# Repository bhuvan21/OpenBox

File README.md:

# OpenBox  
An open source, arduino based fencing scoring box. Created with a low budget in mind (costs ~£50 to build), but maximal portability and functionality.  

The hardware of this fencing box has been meticulously planned, designed, and put together.  
The software for the box is not yet finished, with only the at-home foil practice, as well as some settings being done.  

## Hardware  
All information on the physical build is contain in BUILD.md, within the build subdirectory.

## Software  
There are quite a few test scripts present in /tests/ which can be used for ensuring that all components connected to the microcontroller are functioning correctly.  
The main box script resides in /main/  

## Roadmap
Though still in the development stage, I think this has the potential to become a viable product. I hope to refine my design further and start deploying them in clubs, schools and tournaments.

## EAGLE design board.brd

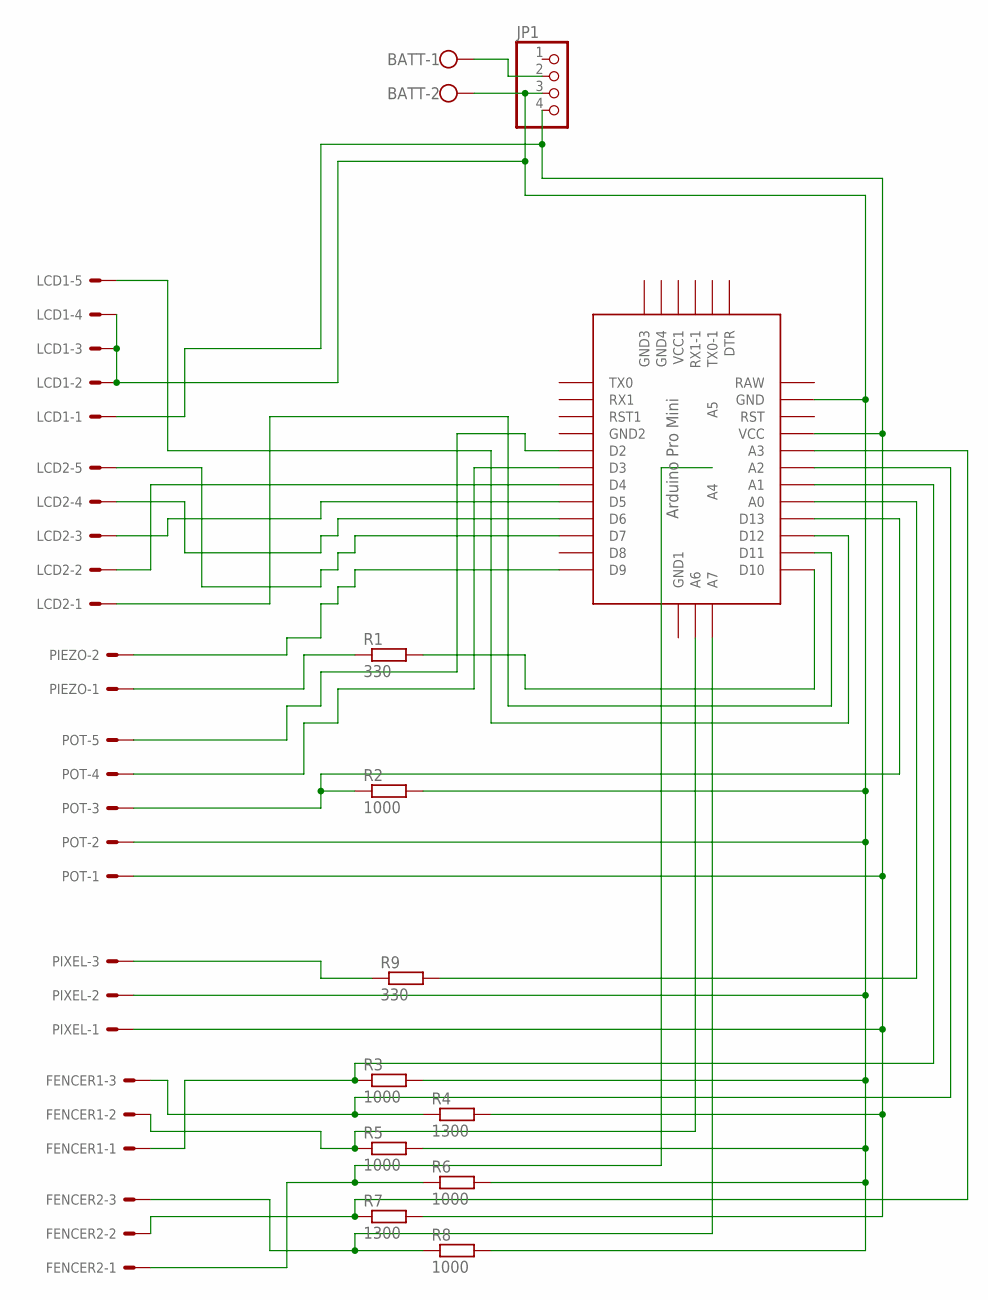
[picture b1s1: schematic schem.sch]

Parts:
BATT: W237-102
FENCER1, FENCER2: 22-27-2031-03; 6410-03
JP1: PINHD-1X4; 1X04
LCD1, LCD2: 22-27-2051-05; 6410-05
PIEZO: 22-27-2021-02; 6410-02
PIXEL: 22-27-2031-03; 6410-03
POT: 22-27-2051-05; 6410-05
R1: 330; 0204/7
R2, R3, R5, R6, R8: 1000; 0204/7
R4, R7: 1300; 0204/7
R9: 330; 0207/10
U$1: ABK-PRO-MINI

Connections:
unnamed: JP1.4, LCD1.1, PIXEL.1, POT.1, R4.2, R7.2, U$1.VCC
unnamed: BATT.2, JP1.3, LCD1.2, LCD1.3, LCD1.4, PIXEL.2, POT.2, R2.2, R3.2, R5.2, R6.2, R8.2, U$1.GND
unnamed: BATT.1, JP1.2
unnamed: LCD2.4, U$1.D6
unnamed: LCD2.1, U$1.D11
unnamed: LCD1.5, U$1.D12
unnamed: LCD2.2, U$1.D4
unnamed: LCD2.3, U$1.D5
unnamed: LCD2.5, U$1.D7
unnamed: PIEZO.2, U$1.D9
unnamed: PIEZO.1, R1.1
unnamed: R1.2, U$1.D10
unnamed: POT.5, U$1.D2
unnamed: POT.4, U$1.D3
unnamed: FENCER1.1, R3.1, U$1.A1
unnamed: POT.3, R2.1, U$1.D13
unnamed: R9.2, U$1.A0
unnamed: FENCER1.3, R4.1, U$1.A2
unnamed: FENCER1.2, R5.1, U$1.A6
unnamed: FENCER2.1, R6.1, U$1.A4
unnamed: FENCER2.3, R8.1, U$1.A7
unnamed: PIXEL.3, R9.1
unnamed: FENCER2.2, R7.1, U$1.A3

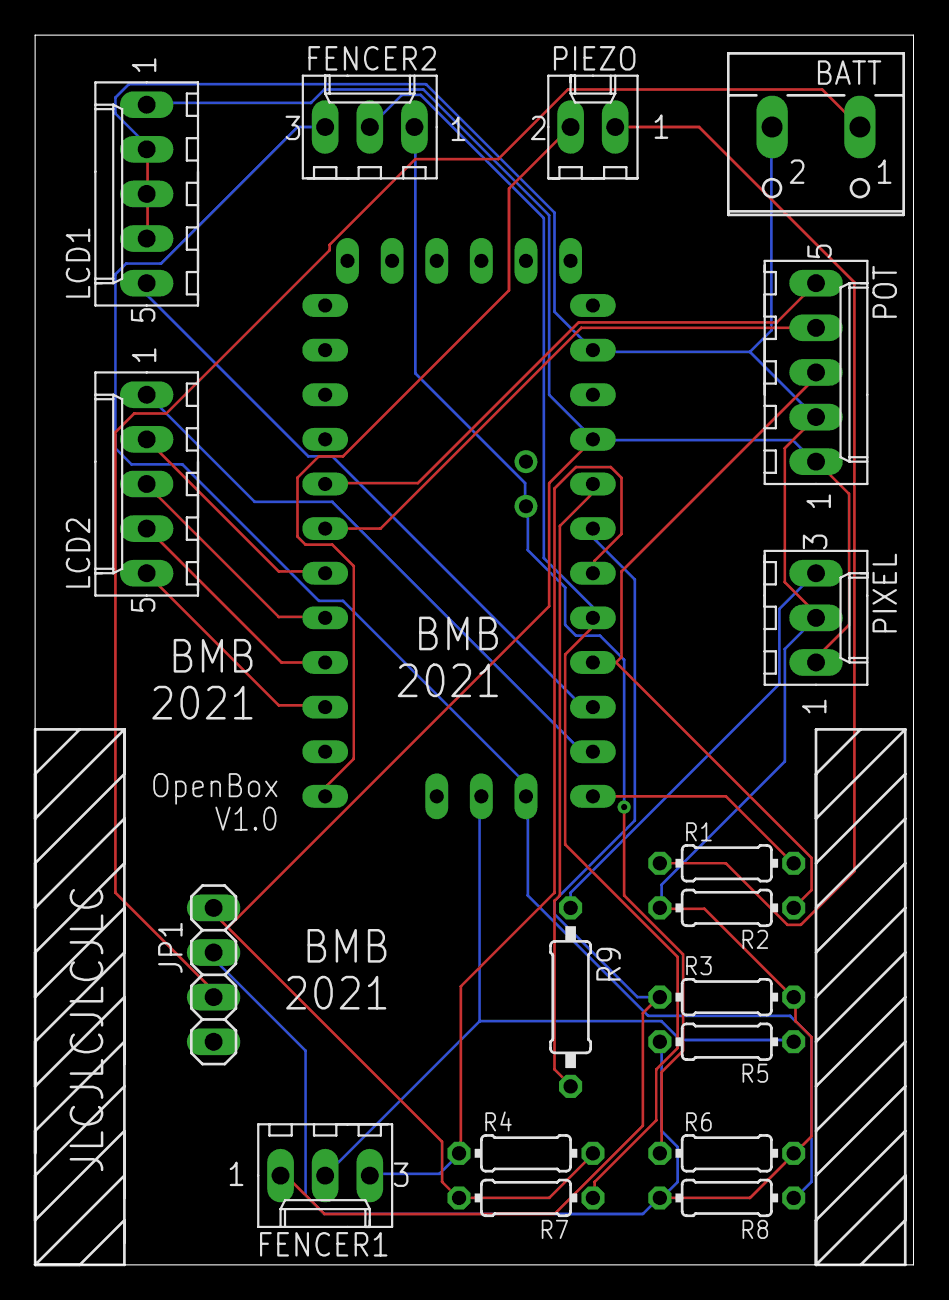
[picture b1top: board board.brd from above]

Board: 2 copper layers, 50.0 x 70.0 mm, 19 parts (0 on the bottom side), 23 nets.

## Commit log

2020-08-03 Initial Commit, test sketches, pcb, stls
2020-08-03 Started basic menus
2020-08-04 Menus now work!
2020-08-06 New Molex version of PCB
2020-08-14 New interrupts
2020-08-17 kind aworks
2020-10-27 Beautification
